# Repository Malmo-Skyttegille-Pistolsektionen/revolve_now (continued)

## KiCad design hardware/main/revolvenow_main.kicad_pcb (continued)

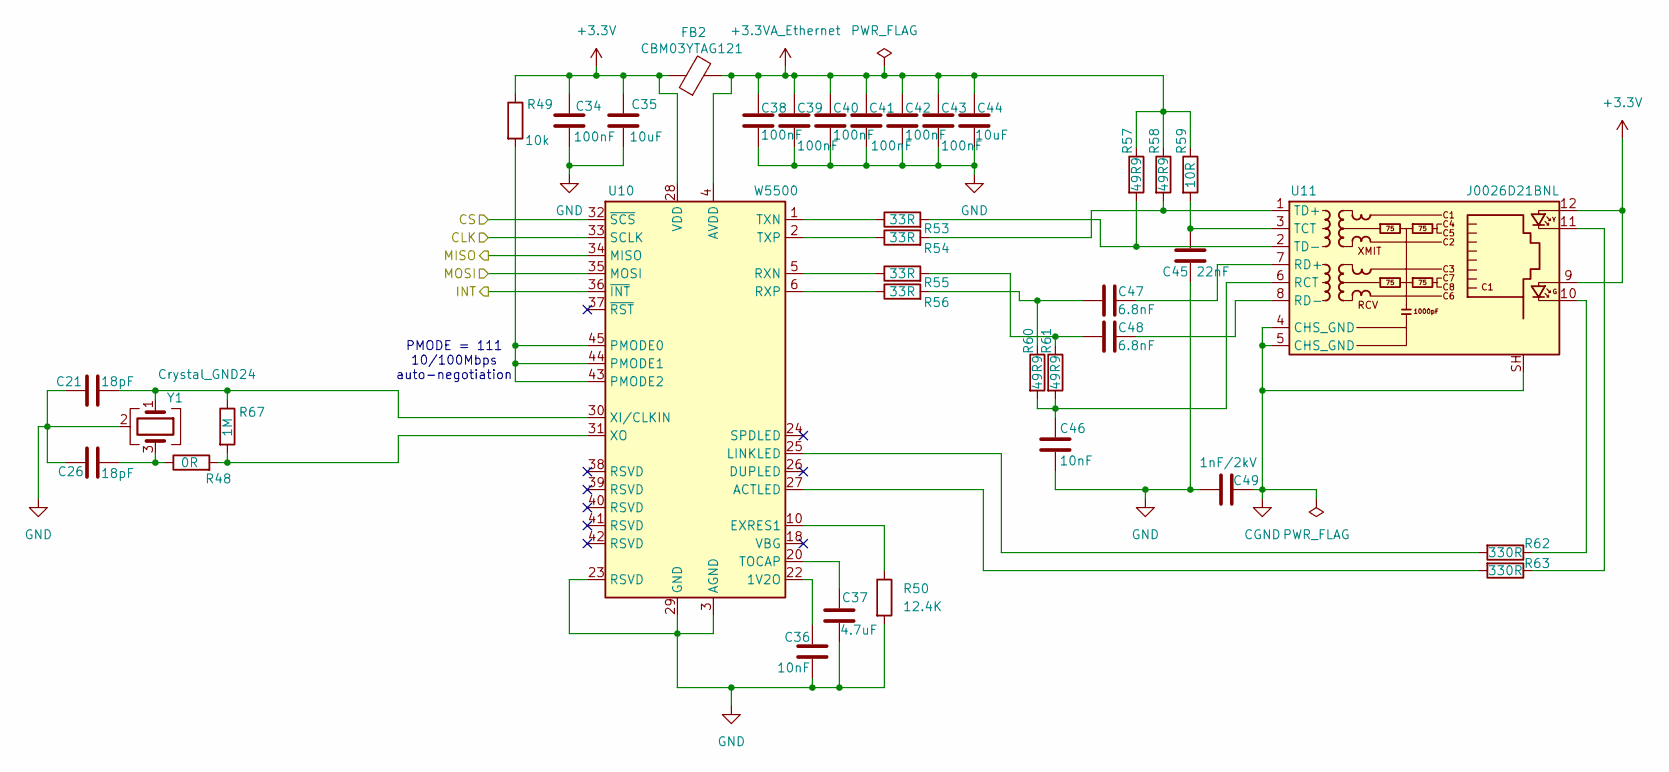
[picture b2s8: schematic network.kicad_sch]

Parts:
C21, C26: 18pF; C_0603_1608Metric_Pad1.08x0.95mm_HandSolder
C34, C38, C39, C40, C41, C42, C43: 100nF; C_0603_1608Metric_Pad1.08x0.95mm_HandSolder
C35, C44: 10uF; C_0603_1608Metric_Pad1.08x0.95mm_HandSolder
C36, C46: 10nF; C_0603_1608Metric_Pad1.08x0.95mm_HandSolder
C37: 4.7uF; C_0603_1608Metric_Pad1.08x0.95mm_HandSolder
C45: 22nF; C_0603_1608Metric_Pad1.08x0.95mm_HandSolder
C47, C48: 6.8nF; C_0603_1608Metric_Pad1.08x0.95mm_HandSolder
C49: 1nF/2kV; C_1206_3216Metric_Pad1.33x1.80mm_HandSolder
FB2: CBM03YTAG121; L_0603_1608Metric_Pad1.05x0.95mm_HandSolder
R48: 0R; R_0603_1608Metric_Pad0.98x0.95mm_HandSolder
R49: 10k; R_0603_1608Metric_Pad0.98x0.95mm_HandSolder
R50: 12.4K; R_0603_1608Metric_Pad0.98x0.95mm_HandSolder
R53, R54, R55, R56: 33R; R_0603_1608Metric_Pad0.98x0.95mm_HandSolder
R57, R58, R60, R61: 49R9; R_0603_1608Metric_Pad0.98x0.95mm_HandSolder
R59: 10R; R_0603_1608Metric_Pad0.98x0.95mm_HandSolder
R62, R63: 330R; R_0603_1608Metric_Pad0.98x0.95mm_HandSolder
R67: 1M; R_0603_1608Metric_Pad0.98x0.95mm_HandSolder
U10: W5500; LQFP-48_7x7mm_P0.5mm
U11: J0026D21BNL; RJ45_PulseJack_MechB
Y1: Crystal_GND24; Crystal_SMD_3225-4Pin_3.2x2.5mm_HandSoldering

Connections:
+3.3V: C34.1, C35.1, FB2.1, R49.1, U10.28 (VDD), U11.9, U11.12; also elsewhere on the board
+3.3VA_Ethernet: C38.1, C39.1, C40.1, C41.1, C42.1, C43.1, C44.1, FB2.2, R57.1, R58.1, R59.1, U10.4 (AVDD), U10.8 (AVDD), U10.11 (AVDD), U10.15 (AVDD), U10.17 (AVDD), U10.21 (AVDD)
/ESP/INT_NET: U10.36 (~INT); also elsewhere on the board
/ESP/SPI_CLK: U10.33 (SCLK); also elsewhere on the board
/ESP/SPI_CS_NET: U10.32 (~SCS); also elsewhere on the board
/ESP/SPI_MISO: U10.34 (MISO); also elsewhere on the board
/ESP/SPI_MOSI: U10.35 (MOSI); also elsewhere on the board
CGND: C49.2, U11.4 (CHS_GND), U11.5 (CHS_GND), U11.SH
GND: C21.1, C26.2, C34.2, C35.2, C36.2, C37.2, C38.2, C39.2, C40.2, C41.2, C42.2, C43.2, C44.2, C45.2, C46.2, C49.1, R50.2, U10.3 (AGND), U10.9 (AGND), U10.14 (AGND), U10.16 (AGND), U10.19 (AGND), U10.23 (RSVD), U10.29 (GND), U10.48 (AGND), Y1.2 (G), Y1.4 (G); also elsewhere on the board
unnamed: C26.1, R48.1, Y1.3
unnamed: C47.1, R56.2, R60.1
unnamed: C48.1, R55.2, R61.1
unnamed: R62.1, U11.10
unnamed: R63.1, U11.11
unnamed: C36.1, U10.22 (1V2O)
unnamed: R63.2, U10.27 (ACTLED)
unnamed: R50.1, U10.10 (EXRES1)
unnamed: R62.2, U10.25 (LINKLED)
unnamed: R49.2, U10.43 (PMODE2), U10.44 (PMODE1), U10.45 (PMODE0)
unnamed: R55.1, U10.5 (RXN)
unnamed: R56.1, U10.6 (RXP)
unnamed: C37.1, U10.20 (TOCAP)
unnamed: R53.1, U10.1 (TXN)
unnamed: R54.1, U10.2 (TXP)
unnamed: C21.2, R67.1, U10.30 (XI/CLKIN), Y1.1
unnamed: R48.2, R67.2, U10.31 (XO)
unnamed: C46.1, R60.2, R61.2, U11.6 (RCT)
unnamed: C47.2, U11.7 (RD+)
unnamed: C48.2, U11.8 (RD-)
unnamed: C45.1, R59.2, U11.3 (TCT)
unnamed: R54.2, R58.2, U11.1 (TD+)
unnamed: R53.2, R57.2, U11.2 (TD-)

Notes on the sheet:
PMODE = 111 10/100Mbps auto-negotiation

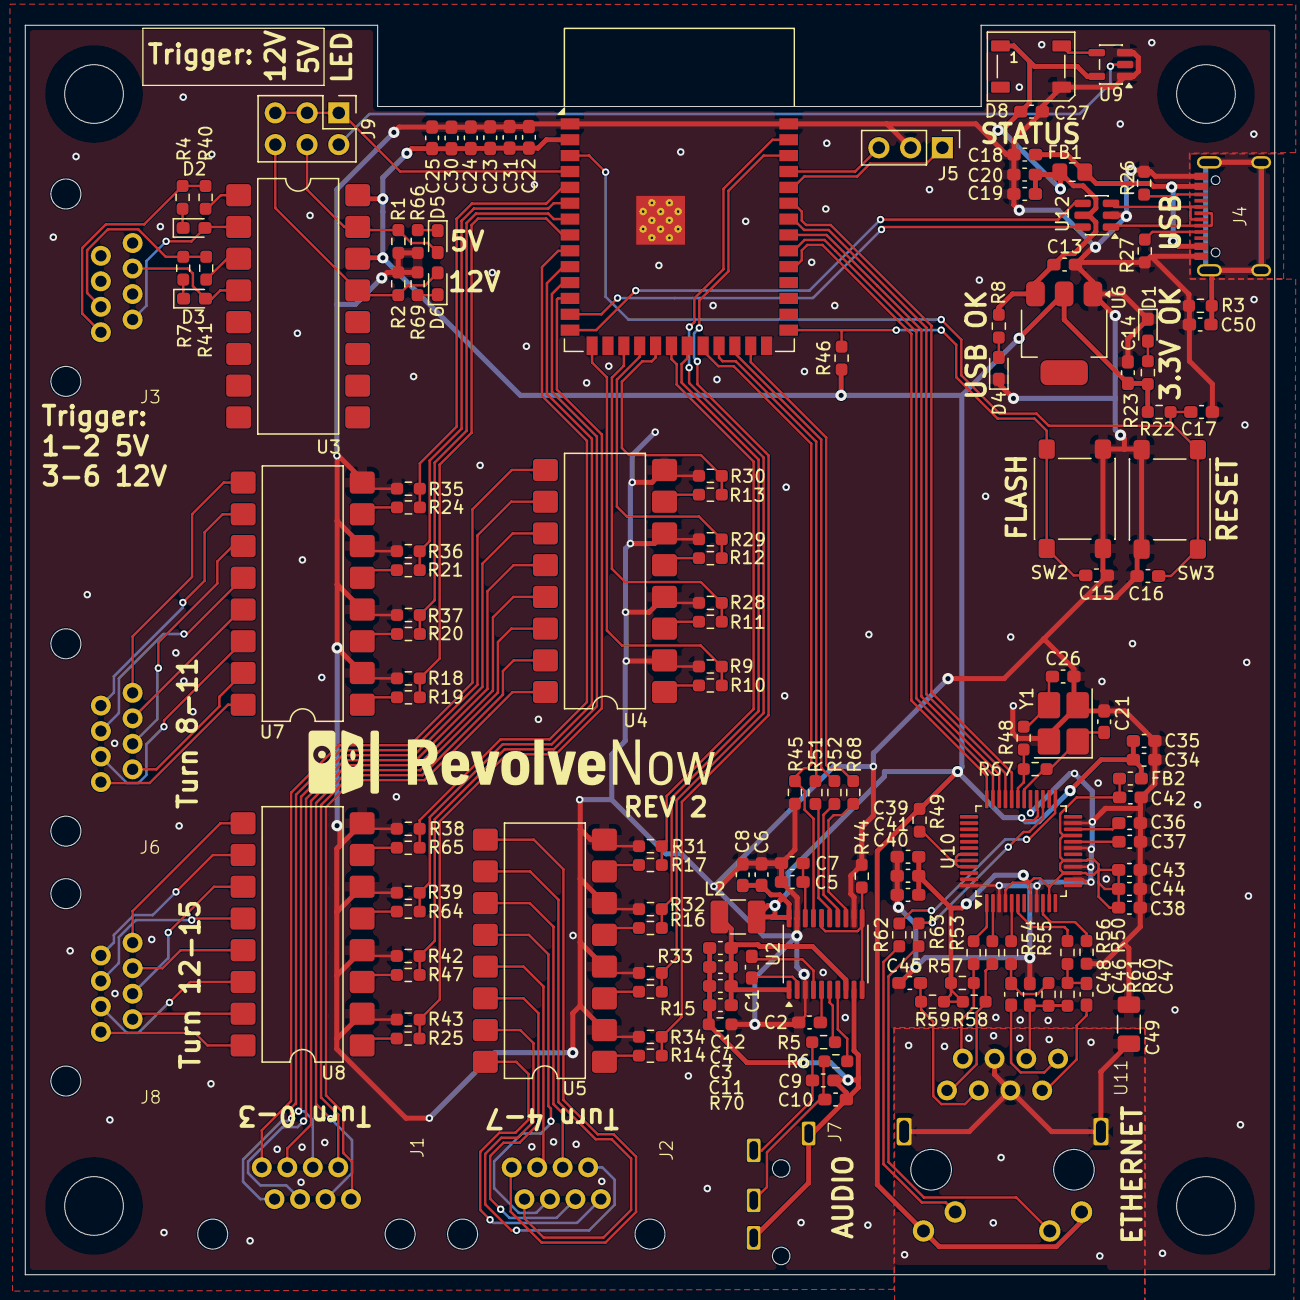
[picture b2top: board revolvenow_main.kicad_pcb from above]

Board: 2 copper layers, 100.0 x 100.0 mm, 150 parts (0 on the bottom side), 144 nets.

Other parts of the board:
D4: GREEN LED; LED_0603_1608Metric_Pad1.05x0.95mm_HandSolder
R8: 220R; R_0603_1608Metric_Pad0.98x0.95mm_HandSolder

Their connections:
+5V: R8.1; also elsewhere on the board
GND: D4.1 (K); also elsewhere on the board
unnamed: D4.2 (A), R8.2
